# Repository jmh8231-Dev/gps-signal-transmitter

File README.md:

# GPS 데이터 송신기 (STM32F103 + ATmega328P)

두 개의 2.4 GHz RF 모듈(nRF24L01+ PA+LNA)과 GNSS, RTC, 환경 센서, 20×4 문자 LCD를 통합한 **원격 GPS 데이터 송신기**이다. 
보드는 **STM32F103C8T6**를 메인 MCU로, **ATmega328P**(Arduino 호환)를 서브 MCU로 사용한다. 서브 MCU는 센서 보조 처리 및
메인 MCU 상태 감시/리셋 보조를 담당한다. 펌웨어는 UBX 프로토콜로 GPS 시간을 수신하여 RTC(DS3231)를 보정하고,
RF/USB/UART로 상태를 송신한다.

---

## 1. 하드웨어 개요

- **MCU**
  - 메인: **STM32F103C8T6** (ST-LINK 20핀 헤더 제공)
  - 서브: **ATmega328P** (AVRISP 헤더, 16 MHz 크리스탈)
- **GNSS**
  - u‑blox **NEO-6M** 모듈(UBX 프로토콜), 백업 배터리(코인셀) 및 PPS/타임펄스 라우팅
- **무선(RF)**
  - **nRF24L01+ PA+LNA** 2개(각각 STM32/Arduino에 1개씩 연결), SMA 안테나
  - **DIP 스위치**로 송신 파워 레벨 설정(MIN/LOW/HIGH/MAX), **모두 OFF→MIN** 기본값
  - 파워 레벨 **LED 인디케이터** 제공
- **표시장치**
  - **20×4 캐릭터 LCD(CLCD2004)**, 백라이트 제어
- **센서**
  - **DHT22**(Temp/Hum) — 기본은 **ATmega328P**가 측정 → UART로 STM32에 전달
  - **CDS**(조도) — 야간에 LED OFF
- **시간/저장소**
  - **RTC: DS3231** (I²C), **EEPROM: 24LC32**
- **인터페이스/디버깅**
  - **USB‑to‑UART**(CDC 장치) 로그, **DFU**(USB) 업데이트
  - **ST‑LINK**, **AVRISP** 업로드 헤더, 수동/자동 리셋 회로

**참고 이미지**
- 스키매틱: `docs/images/schematic.png`
- PCB 레이아웃: `docs/images/pcb_layout.png`
- 동작 사진: `docs/images/photo_running.jpg`

---

## 2. 최종 동작 컨셉

1) **DIP 스위치로 RF 파워 레벨 제어**(STM32는 AUTO 모드 추가), **LED**로 단계 표시  
2) **USB‑to‑UART**로 디버깅/상태 표시(PC 미연결 시 LCD로 표시)  
3) **감시 구조**: STM32는 **IWDG**, ATmega328P는 **STM32에서 모니터링해 필요 시 리셋**  
4) **RTC 보정**: GPS 시간 수신 시 RTC 보정, GPS 부재 시 RTC 시간을 사용해 송신  
5) **2.4 GHz 간섭 방지**: **STM32 먼저 송신 → 신호 후 ATmega 송신**  
6) **DFU 업데이트**: SW 입력 조건에서 자동 리셋 + USB 활성화(펌웨어 업로드 편의성)

---

## 3. DIP 스위치/LED 정책

- **파워 레벨 매핑 (2비트 예시)**  
  `00 → MIN`, `01 → LOW`, `10 → HIGH`, `11 → MAX`  
  *모두 OFF일 경우 MIN로 동작.*
- **LED 표시**  
  레벨별 LED 켜짐(또는 LCD에 현재 단계 표시). 야간에는 **CDS** 감지로 LED OFF.

---

## 4. 펌웨어 구조

### 4.1 STM32 (핵심 루프)
- **GPS(UBX) 파싱** → **RTC(DS3231) 보정** → **LCD 표시(시각/출처/GPIO/전압·온도)** → **RF/USB 전송**
- **타이머(TIM2) 500 ms** 주기 이벤트로 LCD 갱신/주기 송신, **IWDG** 갱신
- **서브 MCU 감시**: UART로 수신된 헬스 바이트 점검, 이상 시 **ATmega328P 리셋 펄스**

주요 구현 포인트:
- UBX **NAV‑TIMEUTC** 메시지 파싱 및 체크섬 확인, GPS 유효 시각 판별(Valid bit)  
- GPS 유효 시 **RTC 보정**, 실패 시 **RTC 시각 사용**  
- LCD 4행 표시: 날짜·시간, 소스(GPS/RTC), 노드수(예약), 온습도(DHT22), VIN/MCU 온도  
- ATmega 리셋은 **최대 횟수 제한** 후 에러 플래그 표시

### 4.2 ATmega328P
- **DHT22 측정** → 결과 프레임을 **UART**로 STM32에 주기 전송  
- 특정 **PWM/헬스 신호 미수신** 시 STM32가 리셋(하드웨어 라인) 실행

---

## 5. 빌드/업로드

- **STM32**: STM32CubeIDE(HAL) 프로젝트. **ST‑LINK**로 프로그래밍. 필요 시 **DFU 모드** 진입 후 USB로 업데이트.
- **ATmega328P**: Arduino IDE 또는 AVR‑GCC. **AVRISP**(J2)로 업로드.
- 업로드 시 RF 모듈 탈착이 필요할 수 있으므로 점퍼를 통해 **Programming / Operation** 모드 선택.

---

## 6. 테스트 절차

1) USB 연결 후 CDC 시리얼 모니터로 로그 확인(보레이트 115200)  
2) GNSS 안테나 연결 → 위성 Lock 후 시간 동기화 확인  
3) DIP 스위치 단계 변경 → LED/LCD 표시 확인, RF 출력 단계 로깅  
4) DHT22 가열 시간 후 값 수신 → LCD 3행 온습도 표시 확인  
5) ISP 점퍼를 ‘Operation’으로 두고 재부팅 → 정상 동작 확인

---

## 7. 파일 트리

```text
gps-tx/
├─ README.md
├─ firmware/
│  ├─ stm32/        # main.c, GPS.c, GPS_Data_Repeater.c 등
│  └─ atmega/       # ATmega328P.ino
└─ docs/
   ├─ images/       # schematic.png, pcb_layout.png, render_top.png, photo_running.jpg
   └─ media/        # demo.mp4 (선택)
```

---

## 8. 이미지

---

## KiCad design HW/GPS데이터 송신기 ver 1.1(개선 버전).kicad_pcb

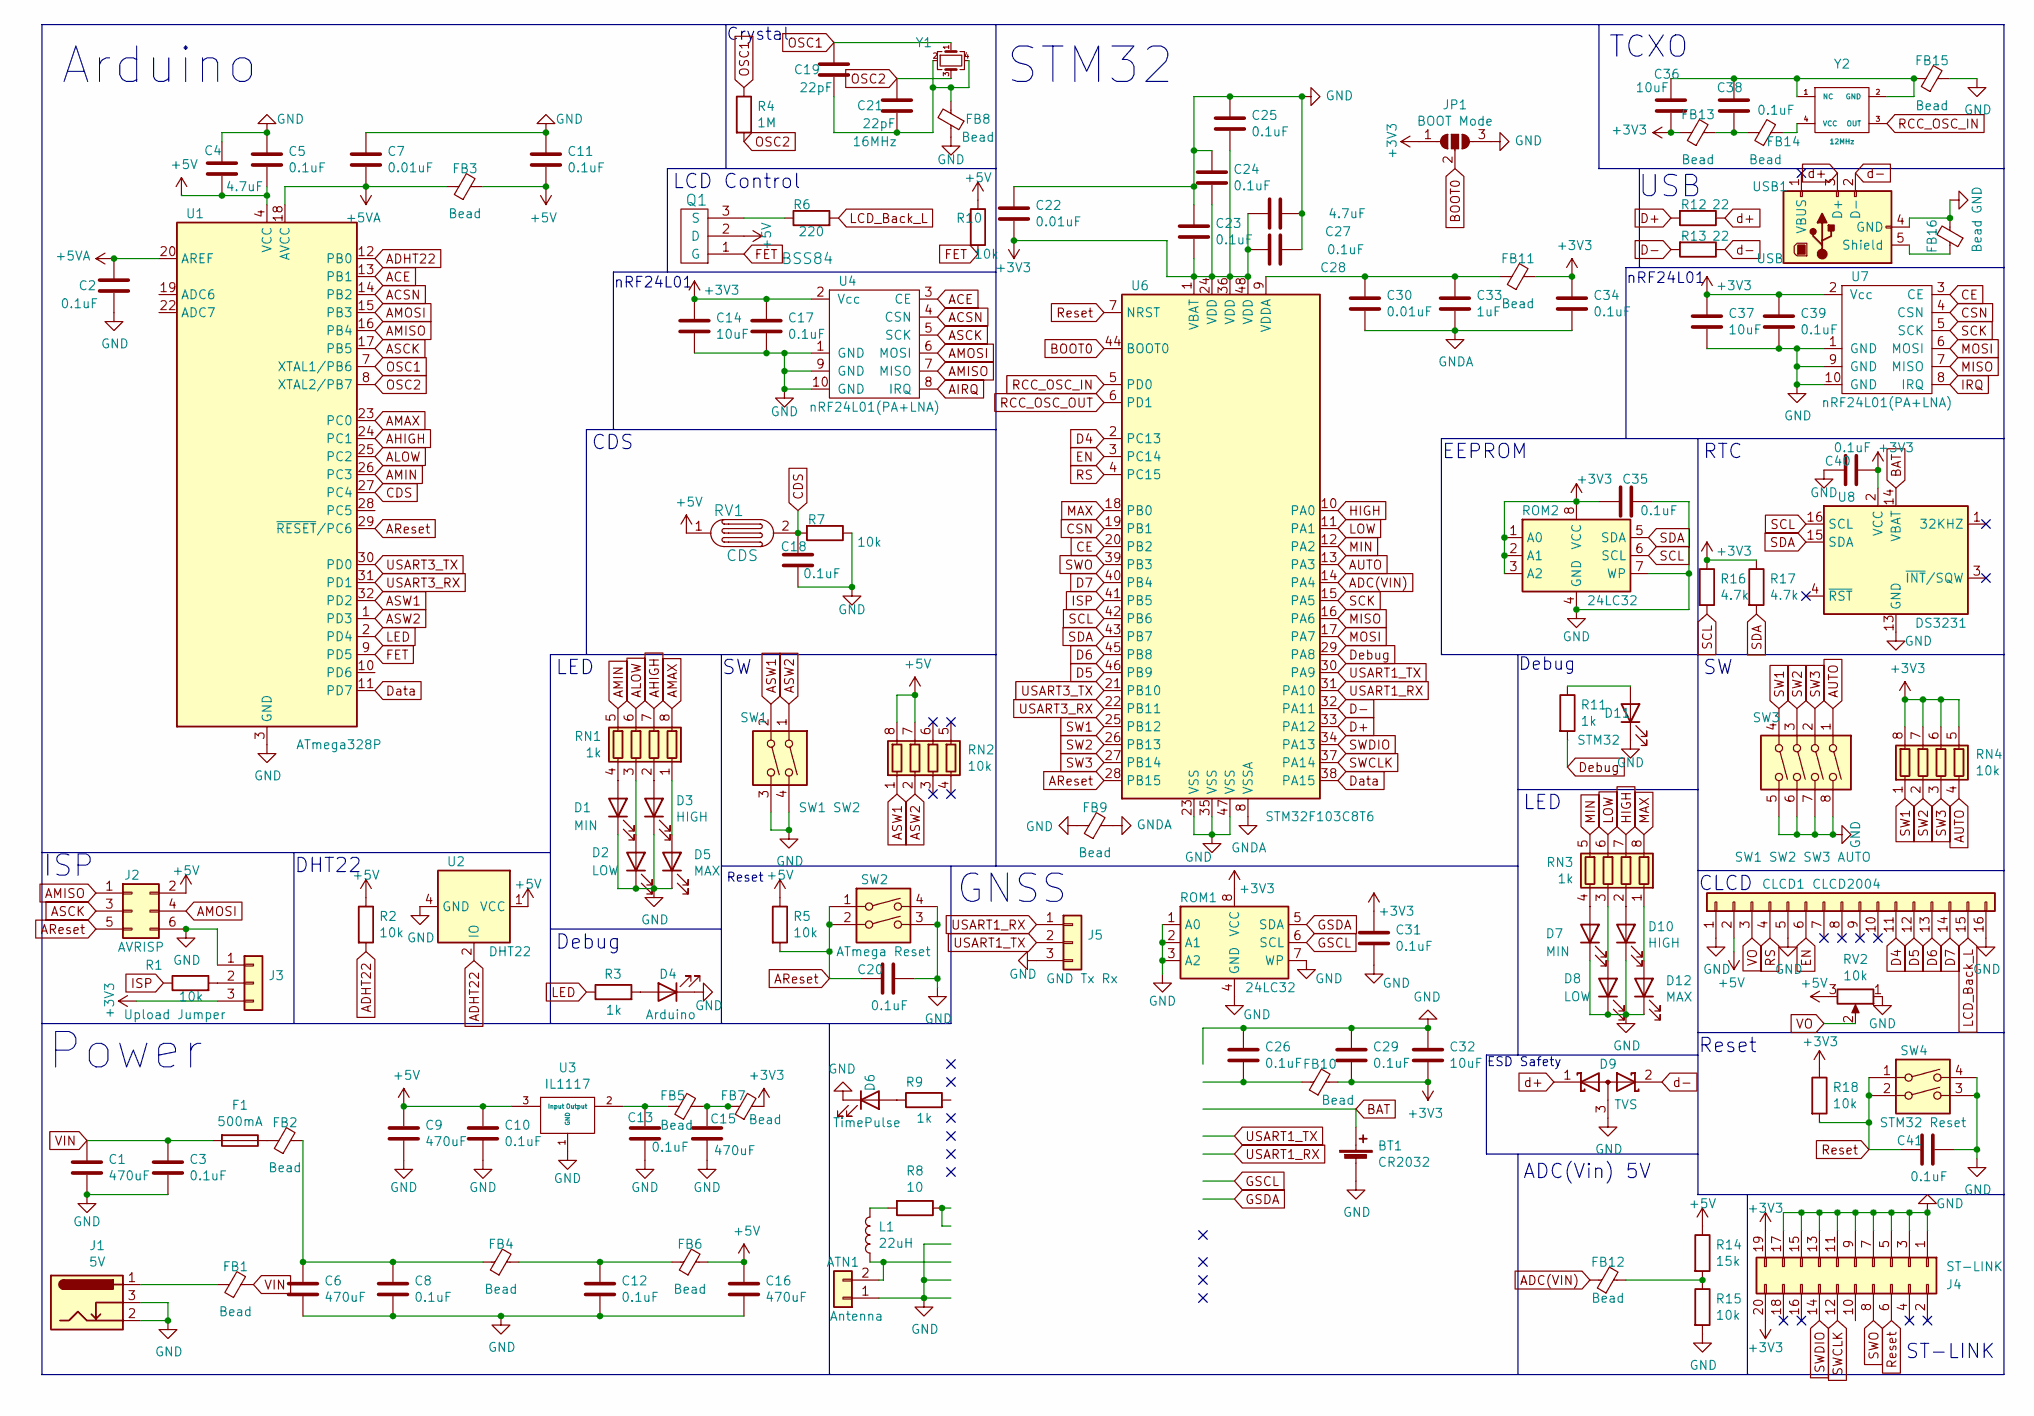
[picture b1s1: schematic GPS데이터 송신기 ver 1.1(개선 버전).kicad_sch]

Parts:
ATN1: Antenna; SMA
BT1: CR2032; BAT-HLD-001
C1, C6, C9, C15, C16: 470uF; MVG25WV470M
C2, C3, C5, C8, C10, C11, C12, C13, C17, C18, C20, C23, C24, C25, C26, C28, C29, C31, C34, C35, C38, C39, C40, C41: 0.1uF; C_0805_2012Metric
C4, C27: 4.7uF; C_0805_2012Metric
C7, C22, C30: 0.01uF; C_0805_2012Metric
C14, C32, C36, C37: 10uF; C_1210_3225Metric
C19, C21: 22pF; C_0805_2012Metric
C33: 1uF; C_0805_2012Metric
CLCD1: CLCD2004; PinHeader_1x16_P2.54mm_Vertical
D1, D7: MIN; LED_0805_2012Metric
D2, D8: LOW; LED_0805_2012Metric
D3, D10: HIGH; LED_0805_2012Metric
D4: Arduino; LED_0805_2012Metric
D5, D12: MAX; LED_0805_2012Metric
D6: TimePulse; LED_0805_2012Metric
D9: TVS; SOT-23
D11: STM32; LED_0805_2012Metric
F1: 500mA; Fuse_1812_4532Metric
FB1, FB2, FB3, FB4, FB5, FB6, FB7, FB8, FB9, FB10, FB11, FB12, FB13, FB14, FB15, FB16: Bead; L_0805_2012Metric
J1: 5V; BarrelJack_Horizontal
J2: AVRISP; PinHeader_2x03_P2.54mm_Vertical
J3: Upload Jumper; PinHeader_1x03_P2.54mm_Vertical
J4: ST-LINK; PinHeader_2x10_P2.54mm_Vertical
J5: GND Tx Rx; PinHeader_1x03_P2.54mm_Vertical
JP1: BOOT Mode; SolderJumper-3_P1.3mm_Open_RoundedPad1.0x1.5mm
L1: 22uH; L_0805_2012Metric
Q1: BSS84; SOT-23
R1, R2, R5, R7, R10, R15, R18: 10k; R_1206_3216Metric
R3, R11: 1k; R_0805_2012Metric
R4: 1M; R_0603_1608Metric
R6: 220; R_1206_3216Metric
R8: 10; R_0805_2012Metric
R9: 1k; R_1206_3216Metric
R12, R13: 22; R_0805_2012Metric
R14: 15k; R_1206_3216Metric
R16, R17: 4.7k; R_0805_2012Metric
RN1, RN3: 1k; R_Array_Convex_4x0402
RN2, RN4: 10k; R_Array_Convex_4x0402
ROM1: 24LC32; TSSOP-8_4.4x3mm_P0.65mm
ROM2: 24LC32; SOIC-8_3.9x4.9mm_P1.27mm
RV1: CDS; R_LDR_4.9x4.2mm_P2.54mm_Vertical
RV2: 10k; 3362P-103LF
SW1: SW1 SW2; SW_DIP_SPSTx02_Slide_9.78x7.26mm_W7.62mm_P2.54mm
SW2: ATmega Reset; SW_SMD_IT-1107
SW3: SW1 SW2 SW3 AUTO; SW_DIP_SPSTx04_Slide_9.78x12.34mm_W7.62mm_P2.54mm
SW4: STM32 Reset; SW_SMD_IT-1107
U1: ATmega328P; TQFP-32_7x7mm_P0.8mm
U2: DHT22; Aosong_DHT11_5.5x12.0_P2.54mm
U3: IL1117; TO-252-2
U4, U7: nRF24L01(PA+LNA)
U6: STM32F103C8T6; LQFP-48_7x7mm_P0.5mm
U8: DS3231; SOIC-16W_7.5x10.3mm_P1.27mm
USB1: USB; USB_B_OST_USB-B1HSxx_Horizontal
Y1: 16MHz; TSX-3225 16.0000MF18X-AC0
Y2: 12MHz; FT5HNBPK12.0-T1

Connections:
+3V3: C14.1, C17.1, C22.2, C23.1, C24.1, C25.1, C27.1, C28.2, C29.2, C31.1, C32.2, C34.1, C35.2, C36.2, C37.1, C39.1, C40.1, FB7.2, FB10.2, FB11.2, FB13.1, J3.3, J4.19, J4.20, JP1.1 (A), R16.1, R17.1, R18.1, RN4.5 (R4.2), RN4.6 (R3.2), RN4.7 (R2.2), RN4.8 (R1.2), ROM1.8 (VCC), ROM2.1 (A0), ROM2.2 (A1), ROM2.3 (A2), ROM2.8 (VCC), U4.2 (Vcc), U6.1 (VBAT), U6.24 (VDD), U6.36 (VDD), U6.48 (VDD), U7.2 (Vcc), U8.2 (VCC)
+5V: C4.1, C5.1, C9.1, C10.1, C11.2, C16.1, CLCD1.2, FB3.2, FB6.2, J2.2, Q1.2 (D), R2.1, R5.1, R10.1, R14.1, RN2.7 (R2.2), RN2.8 (R1.2), RV1.1, RV2.3, U1.4 (VCC), U1.6 (VCC), U2.1 (VCC), U3.3 (Input)
+5VA: C2.2, C7.2, FB3.1, U1.18 (AVCC), U1.20 (AREF)
ACE: U1.13 (PB1), U4.3 (CE)
ACSN: U1.14 (PB2), U4.4 (CSN)
ADC(VIN): FB12.1, U6.14 (PA4)
ADHT22: R2.2, U1.12 (PB0), U2.2 (IO)
AHIGH: RN1.7 (R2.2), U1.24 (PC1)
AIRQ: U4.8 (IRQ)
ALOW: RN1.6 (R3.2), U1.25 (PC2)
AMAX: RN1.8 (R1.2), U1.23 (PC0)
AMIN: RN1.5 (R4.2), U1.26 (PC3)
AMISO: J2.1, U1.16 (PB4), U4.7 (MISO)
AMOSI: J2.4, U1.15 (PB3), U4.6 (MOSI)
AReset: C20.2, J2.5, R5.2, SW2.1, SW2.2, U1.29 (~RESET/PC6), U6.28 (PB15)
ASCK: J2.3, U1.17 (PB5), U4.5 (SCK)
ASW1: RN2.1 (R1.1), SW1.2, U1.32 (PD2)
ASW2: RN2.2 (R2.1), SW1.1, U1.1 (PD3)
AUTO: RN4.4 (R4.1), SW3.1, U6.13 (PA3)
BAT: BT1.1 (+), U8.14 (VBAT); also elsewhere on the board
BOOT0: JP1.2 (C), U6.44 (BOOT0)
CDS: C18.1, R7.2, RV1.2, U1.27 (PC4)
CE: U6.20 (PB2), U7.3 (CE)
CSN: U6.19 (PB1), U7.4 (CSN)
D4: CLCD1.11, U6.2 (PC13)
D5: CLCD1.12, U6.46 (PB9)
D6: CLCD1.13, U6.45 (PB8)
D7: CLCD1.14, U6.40 (PB4)
D+: R12.2, U6.33 (PA12)
D-: R13.2, U6.32 (PA11)
Data: U1.11 (PD7), U6.38 (PA15)
Debug: R11.2, U6.29 (PA8)
EN: CLCD1.6, U6.3 (PC14)
FET: Q1.1 (G), R10.2, U1.9 (PD5)
GND: ATN1.1, BT1.2 (-), C1.2, C2.1, C3.2, C4.2, C5.2, C6.2, C7.1, C8.2, C9.2, C10.2, C11.1, C12.2, C13.2, C14.2, C15.2, C16.2, C17.2, C18.2, C20.1, C22.1, C23.2, C24.2, C25.2, C26.1, C27.2, C28.1, C29.1, C31.2, C32.1, C35.1, C37.2, C39.2, C40.2, C41.1, CLCD1.1, CLCD1.5, CLCD1.16, D1.1 (K), D2.1 (K), D3.1 (K), D4.1 (K), D5.1 (K), D6.1 (K), D7.1 (K), D8.1 (K), D9.3 (A), D10.1 (K), D11.1 (K), D12.1 (K), FB8.1, FB9.1, FB15.2, FB16.2, J1.2, J1.3, J2.6, J3.1, J4.1, J4.3, J4.5, J4.7, J4.9, J4.11, J4.13, J4.15, J4.17, J5.3, JP1.3 (B), R7.1, R15.2, ROM1.1 (A0), ROM1.2 (A1), ROM1.3 (A2), ROM1.4 (GND), ROM1.7 (WP), ROM2.4 (GND), ROM2.7 (WP), RV2.1, SW1.3, SW1.4, SW2.3, SW2.4, SW3.5, SW3.6, SW3.7, SW3.8, SW4.3, SW4.4, U1.3 (GND), U1.5 (GND), U1.21 (GND), U2.4 (GND), U3.1 (GND), U4.1 (GND), U4.9 (GND), U4.10 (GND), U6.23 (VSS), U6.35 (VSS), U6.47 (VSS), U7.1 (GND), U7.9 (GND), U7.10 (GND), U8.5 (GND), U8.6 (GND), U8.7 (GND), U8.8 (GND), U8.9 (GND), U8.10 (GND), U8.11 (GND), U8.12 (GND), U8.13 (GND), USB1.4 (GND); also elsewhere on the board
GNDA: C30.2, C33.2, C34.2, FB9.2, U6.8 (VSSA)
GSCL: ROM1.6 (SCL); also elsewhere on the board
GSDA: ROM1.5 (SDA); also elsewhere on the board
HIGH: RN3.7 (R2.2), U6.10 (PA0)
IRQ: U7.8 (IRQ)
ISP: R1.1, U6.41 (PB5)
LCD_Back_L: CLCD1.15, R6.2
LED: R3.1, U1.2 (PD4)
LOW: RN3.6 (R3.2), U6.11 (PA1)
MAX: RN3.8 (R1.2), U6.18 (PB0)
MIN: RN3.5 (R4.2), U6.12 (PA2)
MISO: U6.16 (PA6), U7.7 (MISO)
MOSI: U6.17 (PA7), U7.6 (MOSI)
unnamed 48: ATN1.2, L1.1; also elsewhere on the board
unnamed: C6.1, C8.1, FB2.2, FB4.1
unnamed: C12.1, FB4.2, FB6.1
unnamed: C13.1, FB5.1, U3.2 (Output)
unnamed: C15.1, FB5.2, FB7.1
unnamed: C19.2, C21.1, FB8.2, Y1.2, Y1.4
unnamed 54: C26.2, FB10.1; also elsewhere on the board
unnamed: C30.1, C33.1, FB11.1, U6.9 (VDDA)
unnamed: C36.1, C38.1, FB15.1, Y2.1 (NC), Y2.2 (GND)
unnamed: C38.2, FB13.2, FB14.1
unnamed: D1.2 (A), RN1.4 (R4.1)
unnamed: D2.2 (A), RN1.3 (R3.1)
unnamed: D3.2 (A), RN1.2 (R2.1)
unnamed: D4.2 (A), R3.2
unnamed: D5.2 (A), RN1.1 (R1.1)
unnamed: D6.2 (A), R9.1
unnamed: D7.2 (A), RN3.4 (R4.1)
unnamed: D8.2 (A), RN3.3 (R3.1)
unnamed: D10.2 (A), RN3.2 (R2.1)
unnamed: D11.2 (A), R11.1
unnamed: D12.2 (A), RN3.1 (R1.1)
unnamed: F1.1, FB2.1
unnamed: FB1.1, J1.1
unnamed: FB12.2, R14.2, R15.1
unnamed: FB14.2, Y2.4 (VCC)
unnamed: FB16.1, USB1.5 (Shield)
unnamed: J3.2, R1.2
unnamed: L1.2, R8.2
unnamed: Q1.3 (S), R6.1
unnamed 86: R8.1; also elsewhere on the board
unnamed 87: R9.2; also elsewhere on the board
OSC1: C19.1, R4.1, U1.7 (XTAL1/PB6), Y1.1
OSC2: C21.2, R4.2, U1.8 (XTAL2/PB7), Y1.3
RCC_OSC_IN: U6.5 (PD0), Y2.3 (OUT)
RCC_OSC_OUT: U6.6 (PD1)
RS: CLCD1.4, U6.4 (PC15)
Reset: C41.2, J4.6, R18.2, SW4.1, SW4.2, U6.7 (NRST)
SCK: U6.15 (PA5), U7.5 (SCK)
SCL: R16.2, ROM2.6 (SCL), U6.42 (PB6), U8.16 (SCL)
SDA: R17.2, ROM2.5 (SDA), U6.43 (PB7), U8.15 (SDA)
SW1: RN4.1 (R1.1), SW3.4, U6.25 (PB12)
SW2: RN4.2 (R2.1), SW3.3, U6.26 (PB13)
SW3: RN4.3 (R3.1), SW3.2, U6.27 (PB14)
SWCLK: J4.12, U6.37 (PA14)
SWDIO: J4.14, U6.34 (PA13)
SWO: J4.8, U6.39 (PB3)
USART1_RX: J5.1, U6.31 (PA10); also elsewhere on the board
USART1_TX: J5.2, U6.30 (PA9); also elsewhere on the board
USART3_RX: U1.31 (PD1), U6.22 (PB11)
USART3_TX: U1.30 (PD0), U6.21 (PB10)
VIN: C1.1, C3.1, F1.2, FB1.2
VO: CLCD1.3, RV2.2
d+: D9.1 (K), R12.1, USB1.3 (D+)
d-: D9.2 (K), R13.1, USB1.2 (D-)

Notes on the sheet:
DHT22
STM32
LED
Debug
ISP
Power
Debug
Arduino
ADC(Vin) 5V
ST-LINK
CDS
TCXO
Reset
ESD Safety
RTC
LCD Control
nRF24L01
CLCD
Crystal
EEPROM
GNSS
USB

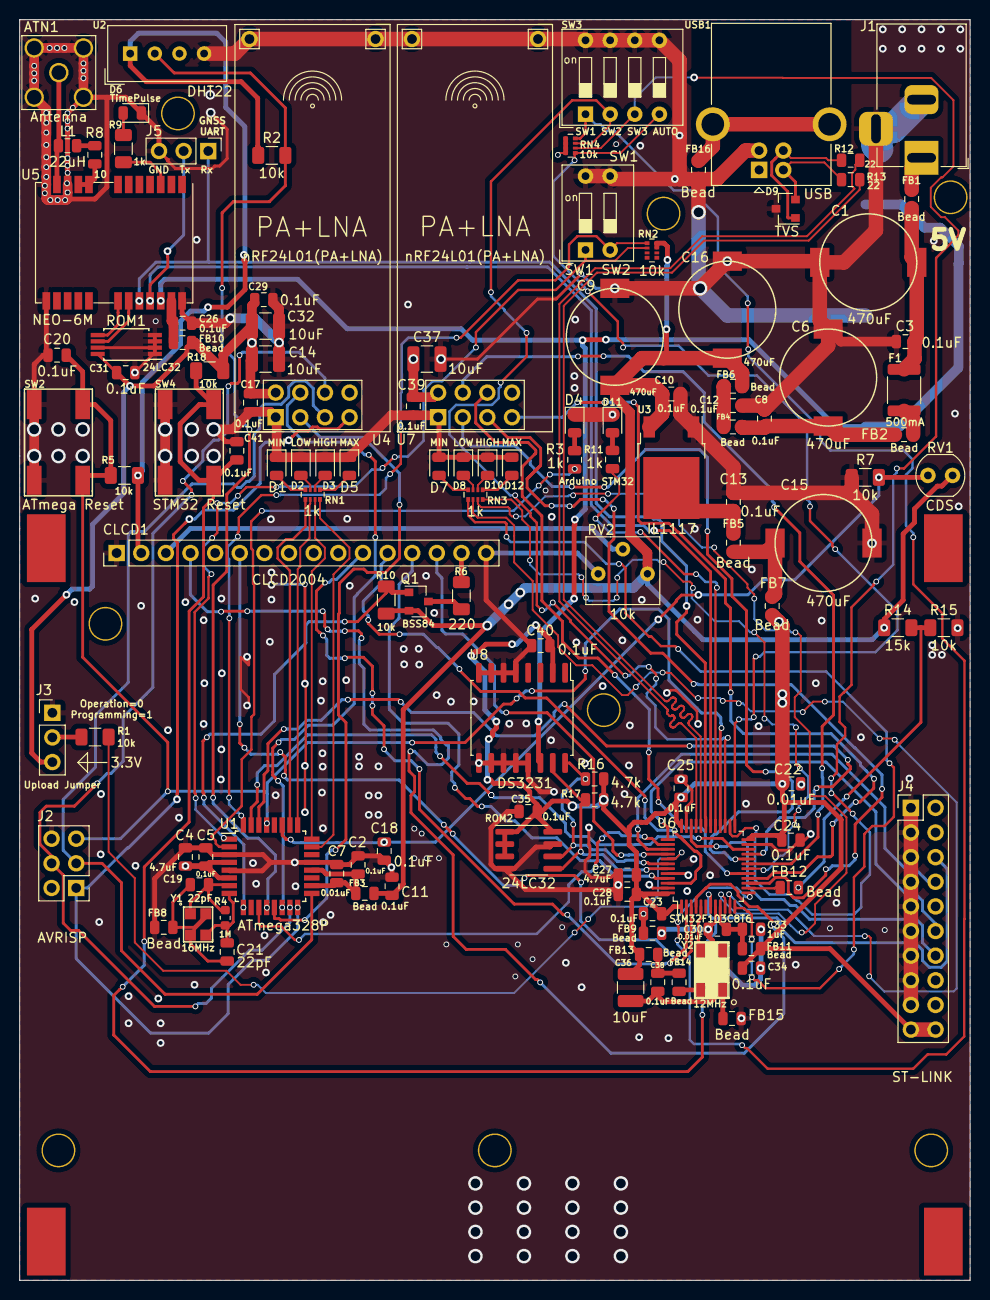
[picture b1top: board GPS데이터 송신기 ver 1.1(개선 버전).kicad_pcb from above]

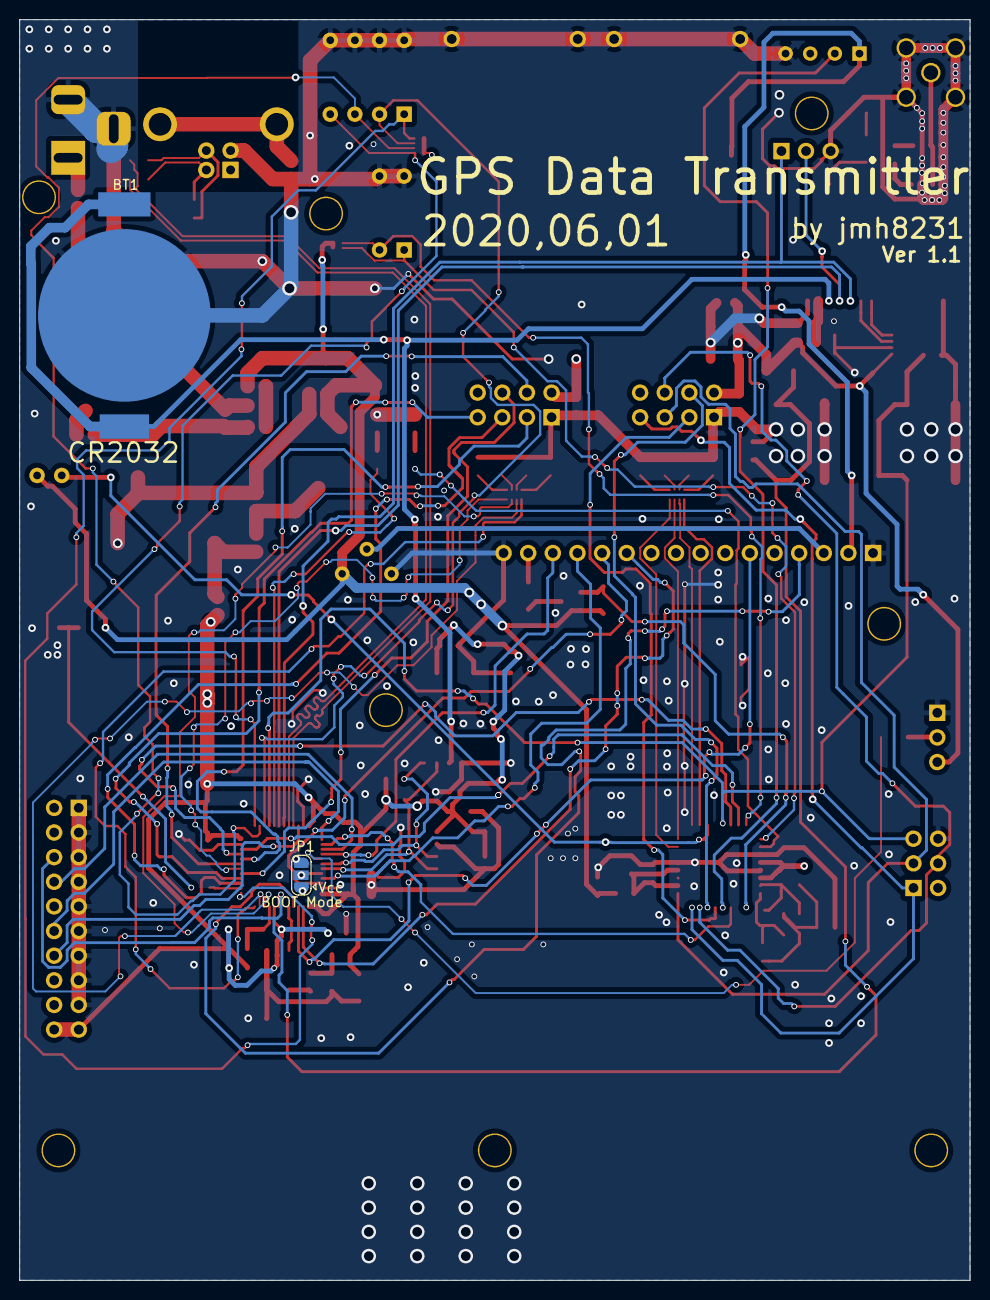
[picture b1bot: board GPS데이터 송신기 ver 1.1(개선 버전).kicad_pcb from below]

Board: 4 copper layers, 98.0 x 130.0 mm, 134 parts (2 on the bottom side), 99 nets.

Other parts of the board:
 : Pad
 #2,  #8,  #9: Pad
 #3,  #4,  #5,  #6,  #7,  #10,  #11,  #12: h
U5: NEO-6M; ublox_NEO

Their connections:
BAT: U5.22; also elsewhere on the board
GND: U5.10, U5.12, U5.13, U5.24; also elsewhere on the board
GSCL: U5.19; also elsewhere on the board
GSDA: U5.18; also elsewhere on the board
unnamed 48: U5.11; also elsewhere on the board
unnamed 54: U5.23; also elsewhere on the board
unnamed 86: U5.8, U5.9; also elsewhere on the board
unnamed 87: U5.3; also elsewhere on the board
USART1_RX: U5.20; also elsewhere on the board
USART1_TX: U5.21; also elsewhere on the board

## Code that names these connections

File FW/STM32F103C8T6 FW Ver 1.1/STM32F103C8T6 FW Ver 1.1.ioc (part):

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Mcu.Name=STM32F103C(8-B)Tx
Mcu.Package=LQFP48
Mcu.UserName=STM32F103C8Tx
PA0-WKUP.GPIOParameters=GPIO_Label
PA0-WKUP.GPIO_Label=LD_HIGH
PA0-WKUP.Signal=GPIO_Output
PA1.GPIOParameters=GPIO_Label
PA1.GPIO_Label=LD_LOW
PA1.Signal=GPIO_Output
PA10.GPIOParameters=GPIO_Label
PA10.GPIO_Label=GPS_Rx
PA10.Mode=Asynchronous
PA10.Signal=USART1_RX
PA11.Mode=Device
PA11.Signal=USB_DM
PA12.Mode=Device
PA12.Signal=USB_DP
PA13.Mode=Serial_Wire
PA13.Signal=SYS_JTMS-SWDIO
PA14.Mode=Serial_Wire
PA14.Signal=SYS_JTCK-SWCLK
PA15.GPIOParameters=GPIO_Label
PA15.GPIO_Label=Status
PA15.Signal=GPIO_Output
PA2.GPIOParameters=GPIO_Label
PA2.GPIO_Label=LD_MIN
PA2.Signal=GPIO_Output
PA3.GPIOParameters=GPIO_Label
PA3.GPIO_Label=SW_4
PA3.Signal=GPIO_Input
PA4.GPIOParameters=GPIO_Label
PA4.GPIO_Label=ADC_VIN
PA4.Signal=ADCx_IN4
PA5.Mode=Full_Duplex_Master
PA5.Signal=SPI1_SCK
PA6.Mode=Full_Duplex_Master
PA6.Signal=SPI1_MISO
PA7.Mode=Full_Duplex_Master
PA7.Signal=SPI1_MOSI
PA8.GPIOParameters=GPIO_Label
PA8.GPIO_Label=LD_Debug
PA8.Signal=GPIO_Output
PA9.GPIOParameters=GPIO_Label
PA9.GPIO_Label=GPS_Tx
PA9.Mode=Asynchronous
PA9.Signal=USART1_TX
PB0.GPIOParameters=GPIO_Label
PB0.GPIO_Label=LD_MAX
PB0.Signal=GPIO_Output
PB1.GPIOParameters=GPIO_Label
PB1.GPIO_Label=SPI1_CS
PB1.Signal=GPIO_Output
PB10.GPIOParameters=GPIO_Label
PB10.GPIO_Label=ATmega328p_Tx
PB10.Mode=Asynchronous
PB10.Signal=USART3_TX
PB11.GPIOParameters=GPIO_Label
PB11.GPIO_Label=ATmega328p_Rx
PB11.Mode=Asynchronous
PB11.Signal=USART3_RX
PB12.GPIOParameters=GPIO_Label
PB12.GPIO_Label=SW_1
PB12.Signal=GPIO_Input
PB13.GPIOParameters=GPIO_Label
PB13.GPIO_Label=SW_2
PB13.Signal=GPIO_Input
PB14.GPIOParameters=GPIO_Label
PB14.GPIO_Label=SW_3
PB14.Signal=GPIO_Input
PB15.GPIOParameters=PinState,GPIO_Label
PB15.GPIO_Label=ATmega328p_Reset
PB15.PinState=GPIO_PIN_SET
PB15.Signal=GPIO_Output
PB2.GPIOParameters=GPIO_Label
PB2.GPIO_Label=SPI1_CE
PB2.Signal=GPIO_Output
PB3.GPIOParameters=GPIO_Label
PB3.GPIO_Label=USB_EN
PB3.Signal=GPIO_Output
PB4.GPIOParameters=GPIO_Label
PB4.GPIO_Label=D7
PB4.Signal=GPIO_Output
PB5.GPIOParameters=GPIO_Label
PB5.GPIO_Label=ISP
PB5.Signal=GPIO_Input
PB6.Mode=I2C
PB6.Signal=I2C1_SCL
PB7.Mode=I2C
PB7.Signal=I2C1_SDA
PB8.GPIOParameters=GPIO_Label
PB8.GPIO_Label=D6
PB8.Signal=GPIO_Output
PB9.GPIOParameters=GPIO_Label
PB9.GPIO_Label=D5
PB9.Signal=GPIO_Output
PC13-TAMPER-RTC.GPIOParameters=GPIO_Label
PC13-TAMPER-RTC.GPIO_Label=D4
PC13-TAMPER-RTC.Signal=GPIO_Output
PC14-OSC32_IN.GPIOParameters=GPIO_Label
PC14-OSC32_IN.GPIO_Label=EN
PC14-OSC32_IN.Signal=GPIO_Output
PC15-OSC32_OUT.GPIOParameters=GPIO_Label
PC15-OSC32_OUT.GPIO_Label=RS
PC15-OSC32_OUT.Signal=GPIO_Output
PD0-OSC_IN.Mode=HSE-External-Oscillator
PD0-OSC_IN.Signal=RCC_OSC_IN
PD1-OSC_OUT.Mode=HSE-External-Oscillator
PD1-OSC_OUT.Signal=RCC_OSC_OUT
RCC.HSE_VALUE=12000000
RCC.SYSCLKFreq_VALUE=72000000
RCC.SYSCLKSource=RCC_SYSCLKSOURCE_PLLCLK
board=custom

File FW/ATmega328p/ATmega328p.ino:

//GPS데이터 송신기

//21.12.12 업데이트 내용: 주변 밝기에 따라 LED 제어 구현

//DHT22를 위한 라이브러리
#include "DHT.h"

//RF모듈을 위한 라이브러리
#include <SPI.h>
#include "RF24.h"

//타이머 인터럽트
#include <MsTimer2.h>

//통신 모듈 설정
RF24 radio(9, 10);//9번핀을 CE, 10번핀을 CSN으로 SPI통신 설정
const byte addresses[6] = "132435";//파이프 주소를 설정

//온습도 센서 설정
DHT DHT(8, DHT22);

//시간 저장 변수
byte TimeData[6];

//RF모듈로 전송할 시간 데이터
char RFTimeData[32];

//주변 밝기를 전송할 변수(STM32)
char LEDflag = 'B';

//주변 밝기를 저장할 변수(아두이노)
bool ledflag = 0;

//STM32로 전송할 데이터
String Data;

//온습도 데이터
//STM32 DMA특성 때문에 더미 데이터 저장
float Hum = 12.34; 
float Temp = 56.78;

int Sean_flag = 0;

void setup() 
{
  //STM32와 UART통신 초기화
  Serial.begin(115200);
  
  //무선통신 모듈 설정
  radio.begin();//무선 통신 모듈 초기화
  radio.setPALevel(RF24_PA_MIN);//거리가 가까운 순으로 RF24_PA_MIN / RF24_PA_LOW / RF24_PA_HIGH / RF24_PA_MAX
  radio.openWritingPipe(addresses);//데이터를 보낼 주소 설정
  radio.stopListening();//송신 모드로 설정

  //센서 초기화
  DHT.begin();
  
  //타이머 인터럽트 설정
  MsTimer2::set(2500, Toggle);// 2500ms 단위로 Toggle() 함수 호출
  MsTimer2::start();//인터럽트 실행
}

//IO핀 레지스터 설정
void PinModeSetUP()
{
  pinMode(2, INPUT);//SW1
  pinMode(3, INPUT);//SW2
  pinMode(4, OUTPUT);//Debug LED
  pinMode(5, OUTPUT);//FET
  pinMode(7, INPUT);//RF모듈 송신 타이밍용
  pinMode(14, OUTPUT);//MIN LED
  pinMode(15, OUTPUT);//LOW LED
  pinMode(16, OUTPUT);//HIGH LED
  pinMode(17, OUTPUT);//MAX LED
}

void TransmitData(char TxData[32])
{
  //MIN모드
  if(digitalRead(2) == LOW && digitalRead(3) == LOW)
  {
    radio.setPALevel(RF24_PA_MIN);

    if(ledflag == 1)
    {
      digitalWrite(14, HIGH);
      digitalWrite(15, LOW);
      digitalWrite(16, LOW);
      digitalWrite(17, LOW);
    }
    else
    {
      digitalWrite(14, LOW);
      digitalWrite(15, LOW);
      digitalWrite(16, LOW);
      digitalWrite(17, LOW);
    }

    radio.write(&TxData, sizeof(TxData));//시간 데이터를 전송 
  }
  
  //LOW모드
  else if(digitalRead(2) == HIGH && digitalRead(3) == LOW)
  {
    radio.setPALevel(RF24_PA_LOW);

    if(ledflag == 1)
    {
      digitalWrite(14, LOW);
      digitalWrite(15, HIGH);
      digitalWrite(16, LOW);
      digitalWrite(17, LOW);
    }
    else
    {
      digitalWrite(14, LOW);
      digitalWrite(15, LOW);
      digitalWrite(16, LOW);
      digitalWrite(17, LOW);
    }

    radio.write(&TxData, sizeof(TxData));//시간 데이터를 전송 
  }

  //HIGH모드
  else if(digitalRead(2) == LOW && digitalRead(3) == HIGH)
  {
    radio.setPALevel(RF24_PA_HIGH);

    if(ledflag == 1)
    {
      digitalWrite(14, LOW);
      digitalWrite(15, LOW);
      digitalWrite(16, HIGH);
      digitalWrite(17, LOW);
    }
    else
    {
      digitalWrite(14, LOW);
      digitalWrite(15, LOW);
      digitalWrite(16, LOW);
      digitalWrite(17, LOW);
    }

    radio.write(&TxData, sizeof(TxData));//시간 데이터를 전송 
  }

  //MAX모드
  else if(digitalRead(2) == HIGH && digitalRead(3) == HIGH)
  {
    radio.setPALevel(RF24_PA_MAX);

    if(ledflag == 1)
    {
      digitalWrite(14, LOW);
      digitalWrite(15, LOW);
      digitalWrite(16, LOW);
      digitalWrite(17, HIGH);
    }
    else
    {
      digitalWrite(14, LOW);
      digitalWrite(15, LOW);
      digitalWrite(16, LOW);
      digitalWrite(17, LOW);
    }

    radio.write(&TxData, sizeof(TxData));//시간 데이터를 전송 
  }
}

//LCD백라이트 컨트롤 함수
void FET_Control()
{          
  //CDS셀 데이터
  int Brightness;

  Brightness = analogRead(A4);

  if(Brightness > 100)
  {
    digitalWrite(5, LOW);
    LEDflag = 'B';
    ledflag = 1;
  }
  else
  {
    digitalWrite(5, HIGH);
    LEDflag = 'C';
    ledflag = 0;
  }
}

void CheckFlag()
{
  if(Sean_flag == 1)
  {
    Sean_flag = 0;

    //습도값을 변수에 저장
    Hum = DHT.readHumidity();
    //온도값을 변수에 저장
    Temp = DHT.readTemperature();
  }
}

void loop()
{
  //리셋을 방지하기 위해 WDT 전송
  Data = String(Hum) + String(Temp) + 'A' + String(LEDflag); 
  Serial.print(Data);
  
  //핀 모드를 정해주는 함수(오류로인해 핀 모드 레지스터가 바뀌어도 바로 수정할수 있다)
  PinModeSetUP(); 
  
  //만약 시간 데이터를 수신하면
  if(Serial.available() > 0)
  {
    //시간데이터를 읽어와 배열에 저장
    for(int i = 0; i < 6; i++)
    {
      TimeData[i] = Serial.read();//시간 데이터 저장
    }
  }
  
  //만약 STM32가 전송을 끝냈으면
  if(digitalRead(7) == LOW)
  {
    //바이트형 배열을 문자열로 변환
    String Time = String(TimeData[0]) + "/" + String(TimeData[1]) + "/" + String(TimeData[2]) + "/" + String(TimeData[3]) + "/" + String(TimeData[4]) + "/" + String(TimeData[5]);

    //문자열을 char형 배열로 변환
    Time.toCharArray(RFTimeData, Time.length() + 1);//수신기로 전송하기 위해 char형 변수로 바꾸어 저장
    
    TransmitData(RFTimeData);//시간정보 전송
  }
  
  //밝기를 센싱하여 LCD백라이트 제어   
  FET_Control();

  CheckFlag();//flag변수들을 확인하는 함수
}

void Toggle()//3초마다 실행되는 함수
{
  if(ledflag == 1)
  {
    //Debug LED 토글
    static boolean output = HIGH;
    digitalWrite(4, output);
    output =! output;
  }
  else
  {
    digitalWrite(4, LOW);
  }
  
    Sean_flag = 1;
}

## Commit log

2025-08-25 GPS Signal Transmitter FW v1.1
2025-08-25 GPS Signal Transmitter HW v1.3
2025-08-25 img update
